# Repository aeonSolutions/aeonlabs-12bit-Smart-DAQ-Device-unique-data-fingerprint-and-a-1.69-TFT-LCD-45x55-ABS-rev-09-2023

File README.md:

[PCB-Prototyping-Catalogue](https://github.com/aeonSolutions/PCB-Prototyping-Catalogue)  >>  [Laboratory Automation](https://github.com/aeonSolutions/PCB-Prototyping-Catalogue/tree/main/Laboratory%20Automation)  >>  [Smart DAQ](https://github.com/aeonSolutions/PCB-Prototyping-Catalogue/tree/main/Smart%20DAQ)  >> [12-bit Smart DAQs](https://github.com/aeonSolutions/PCB-Prototyping-Catalogue/tree/main/Smart%20DAQ/12-bit) >> 12-bit Smart DAQ Device with unique data fingerprint and a 1.69" TFT LCD  45x55 ABS

<br>

# 12bit Smart DAQ Device with unique data fingerprint and a 1.69" TFT LCD 45x55 ABS (revision 10-2023)
This is the repository for revision "10-2023" of the 12-bit Smart DAQ Device with a unique data fingerprint able to do experimental data upload to any data repository.

<br>
<br>

**Status**

Fully working

<br>

## Known faults
- PCB copper track optimizations
- components rearrangement for optimization of PCB track inductance 

<br>
<br>

## Dataverse API C library

This device uses my C++ library to expedite dataverse API integration on smart DAQ devices or elsewhere. Follow the link to its repository:

https://github.com/aeonSolutions/OpenScience-Dataverse-API-C-library

<p align="center">

</p>

<br>
<br>

The photo above is one of the many specimens I purposely fabricated to research self-sensing properties of asphalt mixed with a known content of carbon fibers. This is a 10cm cylinder specimen and on the top is already setup my own design smart #DAQ (get it here on my GitHub ) with the ability to upload LIVE experimental data to a #dataverse.

In the photo above the smart DAQ is installed on an acrylic case and screwed with plastic screws to an acrylic base with the same cross-section area as the specimen to be tested. 
The acrylic base can be bought [here](https://s.click.aliexpress.com/e/_DEGsZaL). And the acrylic case [here](https://s.click.aliexpress.com/e/_Dmudkjt). 

<br>
<br>

### Smart PCB Hardware Specifications
The hardware specifications for the 12bit pcb with dimensions of 23.5x43.5mm are the following:

- QFN 56 Dual Xtensa LX7 Core Processors running up to 240MHz
  -	RISC V ultra-low power co-processor
  - 512Kb RAM (PSRAM max 1 Gb);
  - 16Mb SOIC 8 NOR SPI Flash Memory (max 1Gb);
  - 2.4GHz ISM wireless connectivity;
  - Up to 118 12bit ADC Multiplexed DAQ channels;
- Authentication & Security:
  - SOIC-8 ATSHA204A SHA-256 high-security hardware authentication IC for secure and unique experimental data exchange
- Power management
  - DFN-6 AUR9718 high efficiency step-down 3.3V 1.5A DC converter;
- Onboard sensors:
  - DFN-8 SHT3.x; temperature sensor with a precision of 1.5C;
  - DFN-8 SHT3.x humidity sensor;
  - LGA-14 LSM6DS3 a 6-axis accelerometer and gyroscope;
  - reference voltage sensor calibration with temperature and humidity
- 	External connectivity for up to 118 sensors:
  -  1x I2C pin terminal connector (shared)
  -  1x 12 to 16bit (oversampling & digitization) digital terminal connector (shared)
  -  1x 12 to 16bit (oversampling & digitization) analog terminal connector (shared) with manual scale selection ohmmeter via jumper pin
  -  12 to 16bit (oversampling & digitization) voltage reference analyzer with temperature compensation 
- 1.69 inch TFT IPS LCD  

<br>
<br>

 **In real life this smart DAQ is able to:**
- connect to all kinds of 3V to 5V Digital sensors;
- connect to all kinds of sensors compatible with the I2C protocol. (max 118 sensors simultaneously)
- measure voltage in the range of  [0;3.3V]
- measure electrical resistance [0; 10^6] Ohm 
- do temperature and humidity compensation on all measurements 
- has a voltage reference sensor for improved accuracy on ADC measurements  
- has a motion sensor to know if anyone moved a specimen during an experiment
- ability to show live experimental data on the 1.69-inch TFT IPS LCD  

<br>
<br>

## PCB circuit Schematic 
The PCB circuit schematic is available in PDF located in the folder "PCB Schematic"
<br>

## PCB design files
The PCB gerber files are located in the folder "gerber" and are ready to order online at any PCB fabrication store. (PCBWay, AllPCB, Eurocircuits, etc)
<br>
<br>

<br>
<br>

## Proof of Concept

To test and validate proposed smart DAQ PCB electronics and its firmware as a solution for LIVE experimental data measurements on any test specimen part of a experimental campaign, This PCB electronics is being used to measure a predefined set of variables/parameters to further study several asphalt mixtures with known carbon fiber weight content in the asphalt matrix. Below is a YouTube link to an unedited short video showing one of the experimental setups.

<br />
<br />
<br />

______________________________________________________________________________________________________________________________
### License
2022 Creative Commons Attribution-NonCommercial-ShareAlike 4.0 International

https://creativecommons.org/licenses/by-nc-sa/4.0/

______________________________________________________________________________________________________________________________

<br />
<br />

### Be supportive of my dedication and work towards technology education and buy me a cup of coffee
Buy me a cup of coffee, a slice of pizza or a book to help me study, eat and think new PCB design files.

<br />
<br />

### Make a donation on Paypal
Make a donation on paypal and get a TAX refund*.

### Support all these open hardware projects and become a patreon  
Liked any of my PCB KiCad Designs? Help and Support my open work to all by becomming a LDAD Patreon.
In return I will give a free PCB design in KiCad to all patreon supporters. To learn more go to patreon.com. Link below.

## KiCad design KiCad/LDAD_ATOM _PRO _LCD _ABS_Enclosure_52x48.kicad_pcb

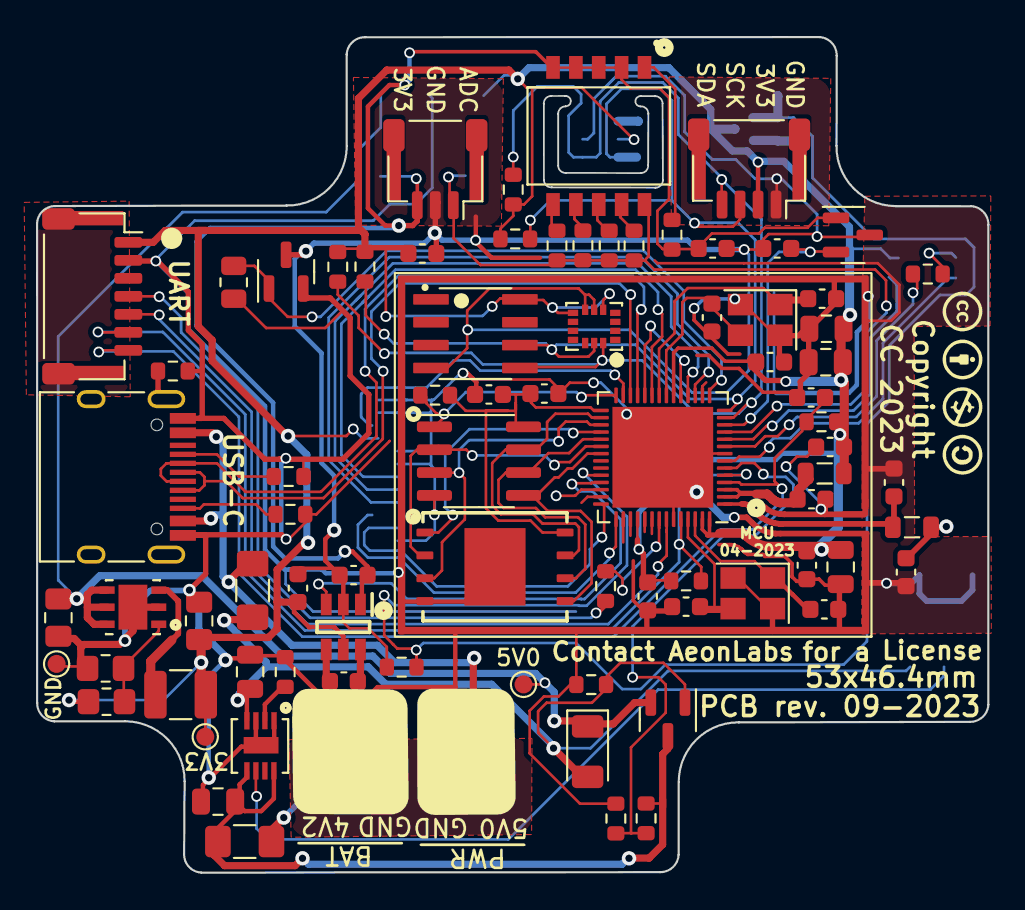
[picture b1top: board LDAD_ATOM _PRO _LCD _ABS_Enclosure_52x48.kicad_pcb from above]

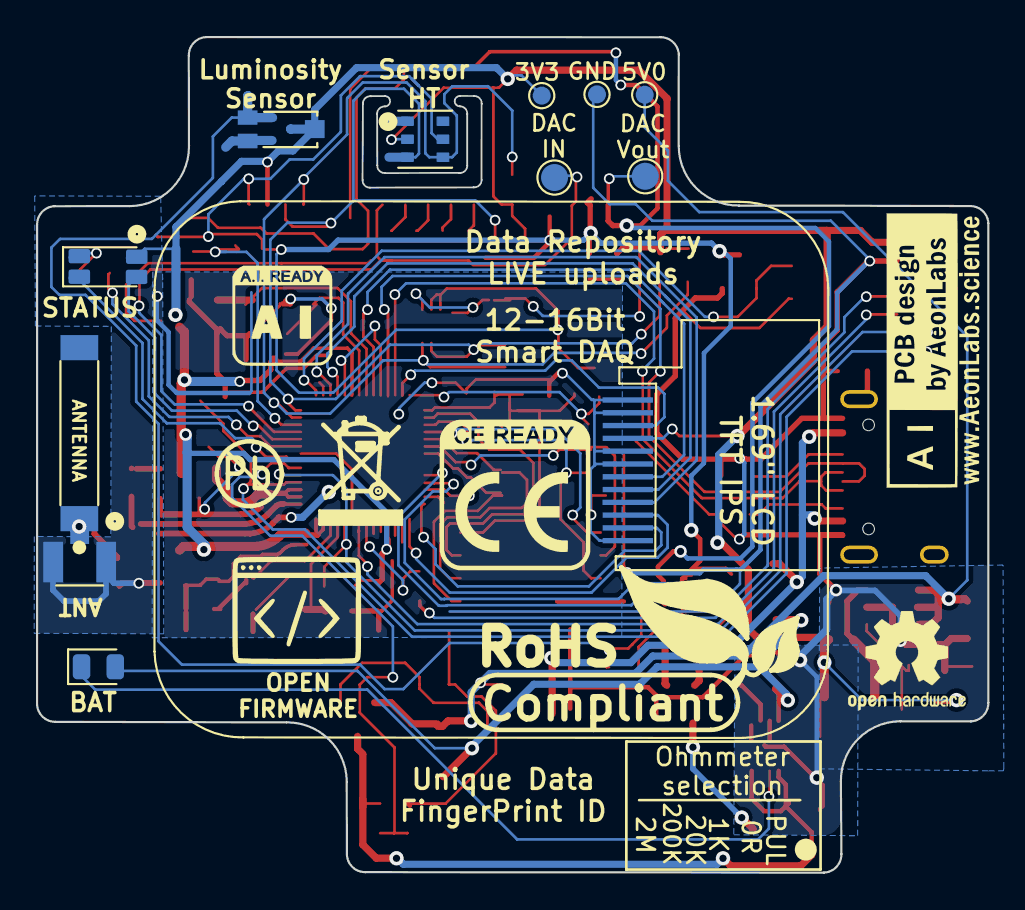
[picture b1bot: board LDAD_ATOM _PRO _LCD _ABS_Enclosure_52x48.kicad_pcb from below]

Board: 2 copper layers, 52.9 x 46.4 mm, 95 parts (13 on the bottom side), 64 nets.

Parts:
ATSHA_C1: 100nF; C_0603_1608Metric
AUR1: AUR9718x_DFN_3x3mm_6_pin; AUR9718 ST1S09 SON95P300X300X100-7N
AUR_C1: 22uF; C_0805_2012Metric_Pad1.18x1.45mm_HandSolder
AUR_C2: 4.7uF; C_0805_2012Metric_Pad1.18x1.45mm_HandSolder
AUR_R1: 75k; R_0805_2012Metric_Pad1.20x1.40mm_HandSolder
AUR_R2: 24k; R_0805_2012Metric_Pad1.20x1.40mm_HandSolder
AUR_l1: 3.3uF; L_1210_3225Metric
BAT_FUSE1: Polyfuse; Fuse_1206_3216Metric_Pad1.42x1.75mm_HandSolder
BAT_SENSE_R1, BAT_SENSE_R2: 100k; R_0603_1608Metric
CN3065_C2: 4.7uF; C_0805_2012Metric
CN3065_R1: 1K8; R_0603_1608Metric
CN3065_STDBY_LED1: LED; LED_0805_2012Metric
CN3965_C1: 22uF; C_0805_2012Metric
DIPSW1: Conn_02x05_Odd_Even; Dip Switch 5pin 1mm SW_DS05-127-2-06BK-SMT-TR
DIP_R1: 4k7; R_0603_1608Metric
DIP_R2: 1k; R_0603_1608Metric
DIP_R3: 20k; R_0603_1608Metric
DIP_R4: 200k; R_0603_1608Metric
DIP_R5: 2M; R_0603_1608Metric
DMP1045U_1: DMP1045U; SOT-23
DMP1045_R1: 10K; R_0603_1608Metric
DMP1045_SCHOT1: D_Schottky; D_1206_3216Metric
EPS1: ESP32-PSRAM_LY68L6400S; SOIC-8_3.9x4.9mm_P1.27mm
ESP32S1: ESP32-S3; QFN-56-1EP_7x7mm_P0.4mm_EP5.6x5.6mm
ESP32_SHIELD1: RFShield_OnePiece; ESP32-S3 GND Shield
ESP_FLASH1: W25Q128JVS; WSON8 FLASH SPI SON127P800X600X80-9N
E_DTR_R1: 10k; R_0603_1608Metric
E_LNA_ANT1: AN9520; 2.4ghZ WIFI ANTENNA AN9520_ANT2-SMD-9.5X2.1X1.0MM
E_LNA_ANT2: U.FL-R-SMT(01); RF Antenna IPEX SMD PCB HRS_U.FL-R-SMT(01)
E_LNA_C1, E_LNA_C2: 2.7pF; C_0603_1608Metric
E_LNA_l1: 1.8nH 5%; L_0805_2012Metric
E_RTS_C1: 100nF; C_0603_1608Metric
E_RTS_R1: 10k; R_0603_1608Metric
E_SPI_C1: 1uF 10% 50V; C_0603_1608Metric
E_SPI_C2: 100nF 10% 16V; C_0603_1608Metric
E_UART_TX_1: 499R; R_0603_1608Metric
E_VDDA_C1: 100nF; C_0603_1608Metric
E_VDDA_C2: 1uF 10% 50V; C_0805_2012Metric
E_VDD_3_C1, E_VDD_3_C2: 10uF 20% 6.3V; C_0805_2012Metric
E_VDD_3_C3, E_VDD_3_C4: 100nF 10% 16V; C_0603_1608Metric
E_VDD_CPU_C1: 100nF 10% 16V; C_0603_1608Metric
E_VDD_L1: 12nH 5%; L_0805_2012Metric
E_VDD_RTC_C1: 100nF 10% 16V; C_0603_1608Metric
E_XTAL32_1: 32.768Mhz 22pF+-10PPM; Crystal_SMD_3225-4Pin_3.2x2.5mm
E_XTAL32_C1, E_XTAL32_C2, E_XTAL40_C1, E_XTAL40_C2: 22pF 5% 50V; C_0603_1608Metric
E_XTAL40_1: 40Mhz 22pF+-10PPM; Crystal_SMD_3225-4Pin_3.2x2.5mm
ExtSW1: Conn_01x03_Female; JST_SH_SM03B-SRSS-TB_1x03-1MP_P1.00mm_Horizontal
ExtSWBAT_PLUG2: Conn_01x03_Female; JST_SH_SM03B-SRSS-TB_1x03-1MP_P1.00mm_Horizontal
HX1: HX4002; HX4002 SOT95 P280X125-6N
HX_C1, HX_C2, HX_C3: 2.2uF; C_0603_1608Metric
I2C_PLUG1: I2C6; JST_SH_SM04B-SRSS-TB_1x04-1MP_P1.00mm_Horizontal
I2C_SCL_R1, I2C_SDA_R1: 10k; R_0603_1608Metric
IMR1, IMR2: 10K; R_0603_1608Metric
IMU1: LSM6DS3; LSM6DS3 Motion Sensor PQFN50P300X250X86-14N
J1: TYPE-C-31-M-12; USB_C_Receptacle_HRO_TYPE-C-31-M-12
JICSP1: Conn_01x07_Socket; JST_SH_SM07B-SRSS-TB_1x07-1MP_P1.00mm_Horizontal
LCD1: Conn_01x12_Male; 1,69 inch LCD IPS TFT
LED1: LED_GBRC; LED_1206_3210_RGB_Metric
LR1: 330R; R_0603_1608Metric
MTRR1: 10k; R_0805_2012Metric
MTRT1: NPN; SOT-23
PSRAM_R1: 100K; R_0603_1608Metric
PWR_FUSE1: Polyfuse; Fuse_1206_3216Metric_Pad1.42x1.75mm_HandSolder
PWR_PLUG1: Screw_Terminal_01x02; JST_SH_SM02B-SRSS-TB_1x02-1MP_P1.00mm_Horizontal
Sign-PbFree: LOGO_PBFREE
Sign-RecycleBin: LOGO_RECYCLEBIN_1
Sign-RoHS: LOGO_ROHS_1
TMPR1: 10K; R_0603_1608Metric
TP1, TP1#2: VIN; TestPoint_Pad_D1.0mm
TP2, TP2#2: VOut; TestPoint_Pad_D1.0mm
TP3, TP3#2: GND; TestPoint_Pad_D1.0mm
U1: MCP1525-TT; SOT-23
U2: ATSHA204A-MAHDA-T; ATSHA204A Auth SOIC8
U3: Battery_charger_CN3065_QFN8; QFN8 3.1x2.9mm QFNn-8 3x3 SON80P400X400X100-9N
U4: AHT20; AHT20 HT Sensor PSON100P300X300X110-6N
U6: TEMT6000; TEMT6000-SEN
USB_PLUG_R1, USB_PLUG_R3: 5k1; R_0603_1608Metric
USB_PLYG_R2: 150K; R_0603_1608Metric
VOLTAGE_REF_C1, VOLTAGE_REF_C2: 100nF; C_0603_1608Metric

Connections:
3V3: ATSHA_C1.2, AUR_C1.1, AUR_R1.1, AUR_l1.1, ESP32S1.20 (VDD3P3_RTC), ESP32S1.46 (VDD3P3_CPU), ESP32S1.55 (VDDA), ESP32S1.56 (VDDA), E_DTR_R1.1, E_RTS_R1.1, E_VDDA_C1.2, E_VDDA_C2.2, E_VDD_3_C1.1, E_VDD_3_C2.1, E_VDD_3_C3.1, E_VDD_CPU_C1.1, E_VDD_L1.1, E_VDD_RTC_C1.1, HX1.5 (VIN), HX_C3.2, I2C_PLUG1.2, I2C_SCL_R1.1, I2C_SDA_R1.2, IMR1.1, IMR2.1, IMU1.5 (VDDIO), IMU1.8 (VDD), JICSP1.1, LCD1.4, LED1.4 (K), TP2.1, TP2#2.1, U2.8 (VCC), U4.2 (VDD), U6.COLLECTOR
3V3_PLUG: DIPSW1.3, DIPSW1.5, DIPSW1.7, DIPSW1.9, DIP_R1.2, ExtSW1.3, HX1.1 (VOUT), HX_C1.1, U1.1 (Vin), VOLTAGE_REF_C1.2
ADC_IN_IO04: DIPSW1.2, DIP_R2.1, DIP_R3.1, DIP_R4.1, DIP_R5.1, ESP32S1.11 (GPIO6/ADC1_CH5), ExtSW1.1
BAT_SENSE_IO21: BAT_SENSE_R1.1, BAT_SENSE_R2.2, ESP32S1.6 (GPIO1/ADC1_CH0)
CHIP_EN: ESP32S1.4 (CHIP_PU/RESET), E_RTS_C1.2, E_RTS_R1.2, JICSP1.7
DAC_CALIBRATION: ESP32S1.19 (GPIO14/ADC2_CH3), ESP32S1.24 (GPIO18/ADC2_CH7/DAC_1)
ESP_GPIO0_BOOT-DTR: ESP32S1.5 (GPIO0/BOOT), ESP32S1.52 (GPIO46), E_DTR_R1.2, JICSP1.6
GND: AUR1.2 (GND), AUR1.7 (GND), AUR_C1.2, AUR_C2.2, AUR_R2.2, BAT_SENSE_R1.2, CN3065_C2.1, CN3065_R1.1, CN3965_C1.1, DMP1045_R1.2, EPS1.4 (VSS), ESP32S1.8 (GPIO3/ADC1_CH2), ESP32S1.51 (GPIO45), ESP32S1.57 (GND), ESP32_SHIELD1.1 (Shield), ESP_FLASH1.4 (GND), ESP_FLASH1.9 (GND), E_LNA_ANT2.1 (GND), E_LNA_ANT2.2 (GND), E_LNA_C1.2, E_LNA_C2.2, E_RTS_C1.1, E_SPI_C1.2, E_SPI_C2.2, E_VDDA_C1.1, E_VDDA_C2.1, E_VDD_3_C1.2, E_VDD_3_C2.2, E_VDD_3_C3.2, E_VDD_3_C4.2, E_VDD_CPU_C1.2, E_VDD_RTC_C1.2, E_XTAL32_1.2, E_XTAL32_1.4, E_XTAL32_C1.2, E_XTAL32_C2.2, E_XTAL40_1.2, E_XTAL40_1.4, E_XTAL40_C1.2, E_XTAL40_C2.2, ExtSWBAT_PLUG2.3, J1.B1, J1.B12, JICSP1.2, LCD1.1, LCD1.2, LCD1.5, LCD1.6, LCD1.12, MTRR1.1, MTRT1.2, PWR_PLUG1.1, TP3.1, TP3#2.1, U3.1 (V_Temp), U3.3 (GND), U3.9 (GND), USB_PLUG_R1.2, USB_PLUG_R3.2, USB_PLYG_R2.2
GNDD: ATSHA_C1.1, ExtSW1.2, ExtSW1.MP, ExtSWBAT_PLUG2.MP, HX1.2 (GND), HX_C1.2, HX_C3.1, I2C_PLUG1.1, I2C_PLUG1.MP, IMU1.6 (GND), IMU1.7 (GND), JICSP1.MP, MTRT1.3, PWR_PLUG1.MP, TMPR1.1, U1.3 (Vss), U2.4 (GND), U4.5 (GND), VOLTAGE_REF_C1.1, VOLTAGE_REF_C2.1
GPIO8_I2C_SDA: ESP32S1.13 (GPIO8/ADC1_CH7), I2C_PLUG1.4, I2C_SDA_R1.1, IMR1.2, IMU1.14 (SDA), U2.5 (SDA), U4.4 (SDA)
GPIO9_I2C_SCL: ESP32S1.14 (GPIO9/ADC1_CH8), I2C_PLUG1.3, I2C_SCL_R1.2, IMR2.2, IMU1.13 (SCL), U2.6 (SCL), U4.3 (SCL)
LCD_CS_IO13: ESP32S1.18 (GPIO13/ADC2_CH2), LCD1.8
LCD_DC_IO17: ESP32S1.23 (GPIO17/ADC2_CH6/DAC_2), LCD1.7
LCD_I2C_SCL_IO12: ESP32S1.17 (GPIO12/ADC2_CH1), LCD1.9
LCD_I2C_SDA_IO38: ESP32S1.43 (GPIO38), LCD1.10
LCD_LED_IO21: ESP32S1.27 (GPIO21), LCD1.3
LCD_RST_IO37: ESP32S1.42 (GPIO37), LCD1.11
LED_B_IO05: ESP32S1.10 (GPIO5/ADC1_CH4), LED1.2 (BA)
LED_G_IO02: ESP32S1.7 (GPIO2/ADC1_CH1), LED1.1 (GA)
LED_R_IO04: ESP32S1.9 (GPIO4/ADC1_CH3), LR1.1
unnamed: AUR1.1 (FB), AUR_R1.2, AUR_R2.1
unnamed: AUR1.3 (SW), AUR_l1.2
unnamed: DIPSW1.1, DIP_R1.1
unnamed: DIPSW1.4, DIP_R2.2
unnamed: DIPSW1.6, DIP_R3.2
unnamed: DIPSW1.8, DIP_R4.2
unnamed: DIPSW1.10, DIP_R5.2
unnamed: ESP32S1.21 (GPIO15/ADC2_CH4/XTAL_32K_P), E_XTAL32_1.3, E_XTAL32_C1.1
unnamed: ESP32S1.22 (GPIO16/ADC2_CH5/XTAL_32K_N), E_XTAL32_1.1, E_XTAL32_C2.1
unnamed: ESP32S1.1 (LNA_IN/RF), E_LNA_C2.1, E_LNA_l1.2
unnamed: ESP32S1.49 (U0TXD/PROG/GPIO43), E_UART_TX_1.2
unnamed: ESP32S1.2 (VDD3P3), ESP32S1.3 (VDD3P3), E_VDD_3_C4.1, E_VDD_L1.2
unnamed: ESP32S1.53 (XTAL_N), E_XTAL40_1.3, E_XTAL40_C2.1
unnamed: ESP32S1.54 (XTAL_P), E_XTAL40_1.1, E_XTAL40_C1.1
unnamed: E_LNA_ANT1.1, E_LNA_ANT2.3 (SIG), E_LNA_C1.1, E_LNA_l1.1
unnamed: HX1.6 (C+), HX_C2.1
unnamed: HX1.4 (C-), HX_C2.2
unnamed: J1.A5 (CC1), USB_PLUG_R3.1
unnamed: J1.B5 (CC2), USB_PLUG_R1.1
unnamed: J1.S1 (SHIELD), USB_PLYG_R2.1
unnamed: LED1.3 (RA), LR1.2
unnamed: CN3065_R1.2, U3.2 (I_SET)
PERIPHERALS_PWR_EN_IO10: ESP32S1.15 (GPIO10/ADC1_CH9), MTRR1.2, MTRT1.1
PLUG_PWR_3V3_EN_IO38: ESP32S1.39 (GPIO34), HX1.3 (EN)
RXD0: ESP32S1.50 (U0RXD/PROG/GPIO44), JICSP1.5
SPICLK: EPS1.6 (SCLK), ESP32S1.33 (SPICLK/GPIO30), ESP_FLASH1.6 (CLK)
SPICS0: ESP32S1.32 (SPICS0/GPIO29), ESP_FLASH1.1 (~CS)
SPICS1: EPS1.1 (~CE), ESP32S1.28 (SPI_CS1/GPIO26), PSRAM_R1.1
SPID: EPS1.5 (SiO0), ESP32S1.35 (SPID/GPIO32), ESP_FLASH1.5 (DI(IO0))
SPIHD: EPS1.7 (SIO3), ESP32S1.30 (SPIHD/GPIO27), ESP_FLASH1.7 (IO3)
SPIQ: EPS1.2 (SIO1), ESP32S1.34 (SPIQ/GPIO31), ESP_FLASH1.2 (DO(IO1))
SPIWP: EPS1.3 (SIO2), ESP32S1.31 (SPIWP/GPIO28), ESP_FLASH1.3 (IO2)
STDBY_LED_G: CN3065_STDBY_LED1.1 (K), U3.6 (LED_DONE)
TEMT6000_IO33: ESP32S1.38 (GPIO33), TMPR1.2, U6.EMITTER
TXD0: E_UART_TX_1.1, JICSP1.4
USB_5V0: CN3065_STDBY_LED1.2 (A), CN3965_C1.2, DMP1045U_1.1, DMP1045_R1.1, DMP1045_SCHOT1.2 (A), PWR_FUSE1.1, U3.4 (VIN)
USB_5V0F: J1.A4, J1.A9, PWR_FUSE1.2, PWR_PLUG1.2
USB_D+: ESP32S1.26 (GPIO20/USB_D+/ADC2_CH9), J1.A6 (DP1), J1.B6 (DP2)
USB_D-: ESP32S1.25 (GPIO19/USB_D-/ADC2_CH8), J1.A7 (DN1), J1.B7 (DN2)
VDD_SPI: EPS1.8 (VCC), ESP32S1.29 (VDD_SPI), ESP_FLASH1.8 (VCC), E_SPI_C1.1, E_SPI_C2.1, PSRAM_R1.2
VIN: AUR1.4 (VIN_SW), AUR1.5 (VIN_A), AUR1.6 (EN), AUR_C2.1, DMP1045U_1.2, DMP1045_SCHOT1.1 (K), TP1.1, TP1#2.1
VIN_BAT: BAT_FUSE1.1, BAT_SENSE_R2.1, CN3065_C2.2, DMP1045U_1.3, U3.5 (BAT+), U3.8 (FB)
VIN_BATF: BAT_FUSE1.2, ExtSWBAT_PLUG2.1
VOLTAGE_REF_IO07: ESP32S1.12 (GPIO7/ADC1_CH6), U1.2 (Vout), VOLTAGE_REF_C2.2
